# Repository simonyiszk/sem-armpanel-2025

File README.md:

# STM32F070 mikrokontrolleres ARM fejlesztőpanel a<br/> Schönherz Elektronikai Műhely 2025-ös<br/> alapozó tanfolyamához

Fícsörök:
- Kenyérvágódeszkával kompatibilis kialakítás
- Feliratozott lábak
- USB-C csatlakozó
- Integrált CMSIS-DAP programozó áramkör
- Visszajelző LED-ek: tápfeszültség, programozó/debugger üzemmód, valamint USER LED a PA6-os lábon
- RESET gomb

A mikrovezérlőhöz tartozó dokumentáció itt érhető el:<br/> [https://www.st.com/en/microcontrollers-microprocessors/stm32f070f6.html#documentation](https://www.st.com/en/microcontrollers-microprocessors/stm32f070f6.html#documentation)

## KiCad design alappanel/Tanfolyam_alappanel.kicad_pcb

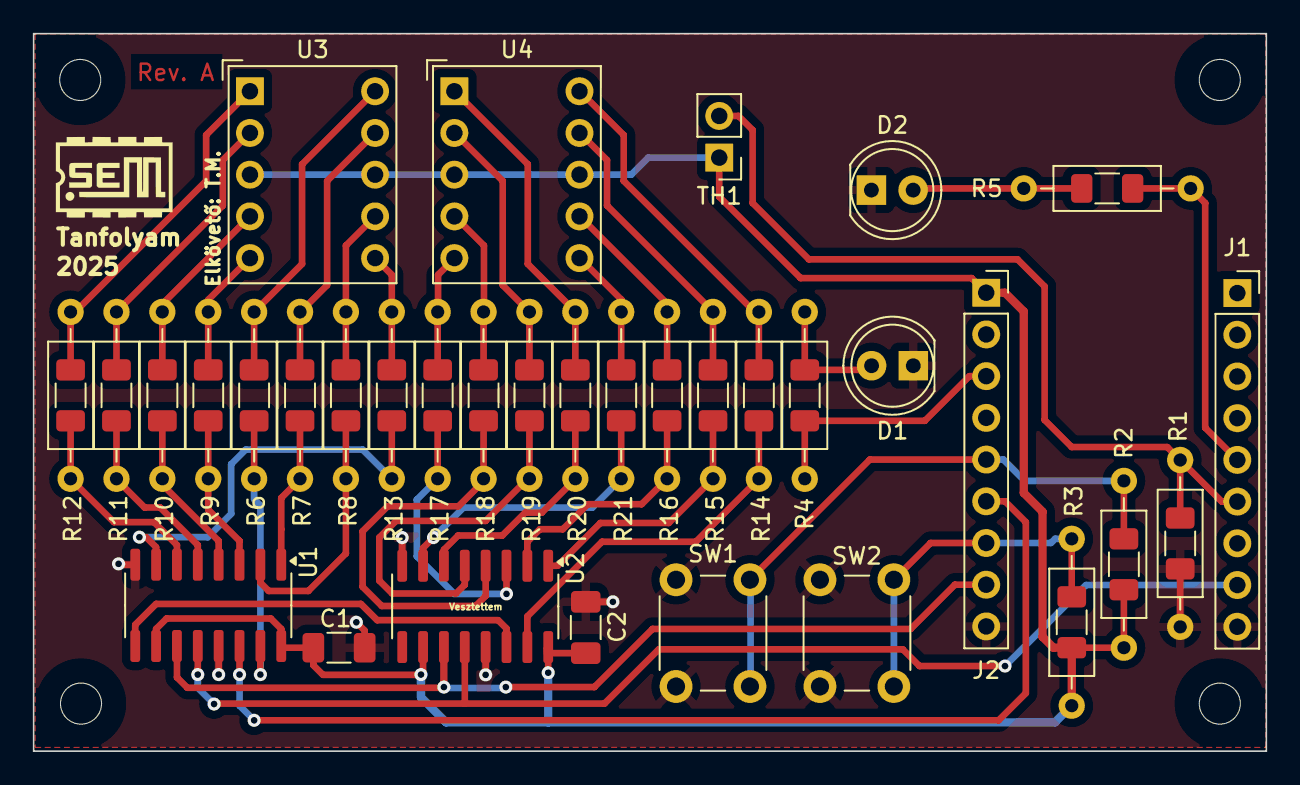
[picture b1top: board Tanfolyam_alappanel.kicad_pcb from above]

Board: 2 copper layers, 75.1 x 43.7 mm, 34 parts (0 on the bottom side), 45 nets.

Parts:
C1, C2: 100n; C_1206_3216Metric_Pad1.33x1.80mm_HandSolder
D1, D2: LED; LED_D5.0mm
J1, J2: Connector; PinSocket_1x09_P2.54mm_Vertical
R1, R2, R3: 10k; R_1206_THT
R4, R5, R6, R7, R8, R9, R10, R11, R12, R13, R14, R15, R16, R17, R18, R19, R20, R21: 220; R_1206_THT
SW1, SW2: SW_Push; SW_PUSH_6mm
TH1: NTC; PinHeader_1x02_P2.54mm_Vertical
U1, U2: 74HC595; SOIC-16_3.9x9.9mm_P1.27mm
U3, U4: SA39-11SRWA; Sx39-1xxxxx

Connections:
+3.3V: C1.1, C2.1, J2.1, R2.1, R3.1, TH1.1, U1.10 (~SRCLR), U1.16 (VCC), U2.10 (~SRCLR), U2.16 (VCC), U3.3 (CA), U3.8 (CA), U4.3 (CA), U4.8 (CA)
/PA0: J1.5, R5.1
/PA1: J1.6, R1.1, TH1.2
/PA4: J1.8, U1.12 (RCLK), U2.12 (RCLK)
/PA5: J2.8, U1.11 (SRCLK), U2.11 (SRCLK)
/PA6: J2.7, R3.2, SW2.1
/PA7: J2.6, U1.14 (SER)
/PA10: J2.3, R4.1
/PB1: J2.5, R2.2, SW1.1
GND: C1.2, C2.2, D1.1 (K), D2.1 (K), J1.9, J2.9, R1.2, SW1.2, SW2.2, U1.8 (GND), U1.13 (~OE), U2.8 (GND), U2.13 (~OE)
unnamed: D1.2 (A), R4.2
unnamed: D2.2 (A), R5.2
unnamed: R6.1, U1.15 (QA)
unnamed: R7.1, U1.1 (QB)
unnamed: R8.1, U1.2 (QC)
unnamed: R9.1, U1.3 (QD)
unnamed: R10.1, U1.4 (QE)
unnamed: R11.1, U1.5 (QF)
unnamed: R12.1, U1.6 (QG)
unnamed: U1.9 (QH'), U2.14 (SER)
unnamed: R13.1, U1.7 (QH)
unnamed: R14.1, U2.15 (QA)
unnamed: R15.1, U2.1 (QB)
unnamed: R16.1, U2.2 (QC)
unnamed: R17.1, U2.3 (QD)
unnamed: R18.1, U2.4 (QE)
unnamed: R19.1, U2.5 (QF)
unnamed: R20.1, U2.6 (QG)
unnamed: R21.1, U2.7 (QH)
unnamed: R6.2, U3.10 (A)
unnamed: R7.2, U3.9 (B)
unnamed: R8.2, U3.7 (C)
unnamed: R9.2, U3.5 (D)
unnamed: R13.2, U3.6 (DP)
unnamed: R10.2, U3.4 (E)
unnamed: R11.2, U3.2 (F)
unnamed: R12.2, U3.1 (G)
unnamed: R14.2, U4.10 (A)
unnamed: R15.2, U4.9 (B)
unnamed: R16.2, U4.7 (C)
unnamed: R17.2, U4.5 (D)
unnamed: R21.2, U4.6 (DP)
unnamed: R18.2, U4.4 (E)
unnamed: R19.2, U4.2 (F)
unnamed: R20.2, U4.1 (G)

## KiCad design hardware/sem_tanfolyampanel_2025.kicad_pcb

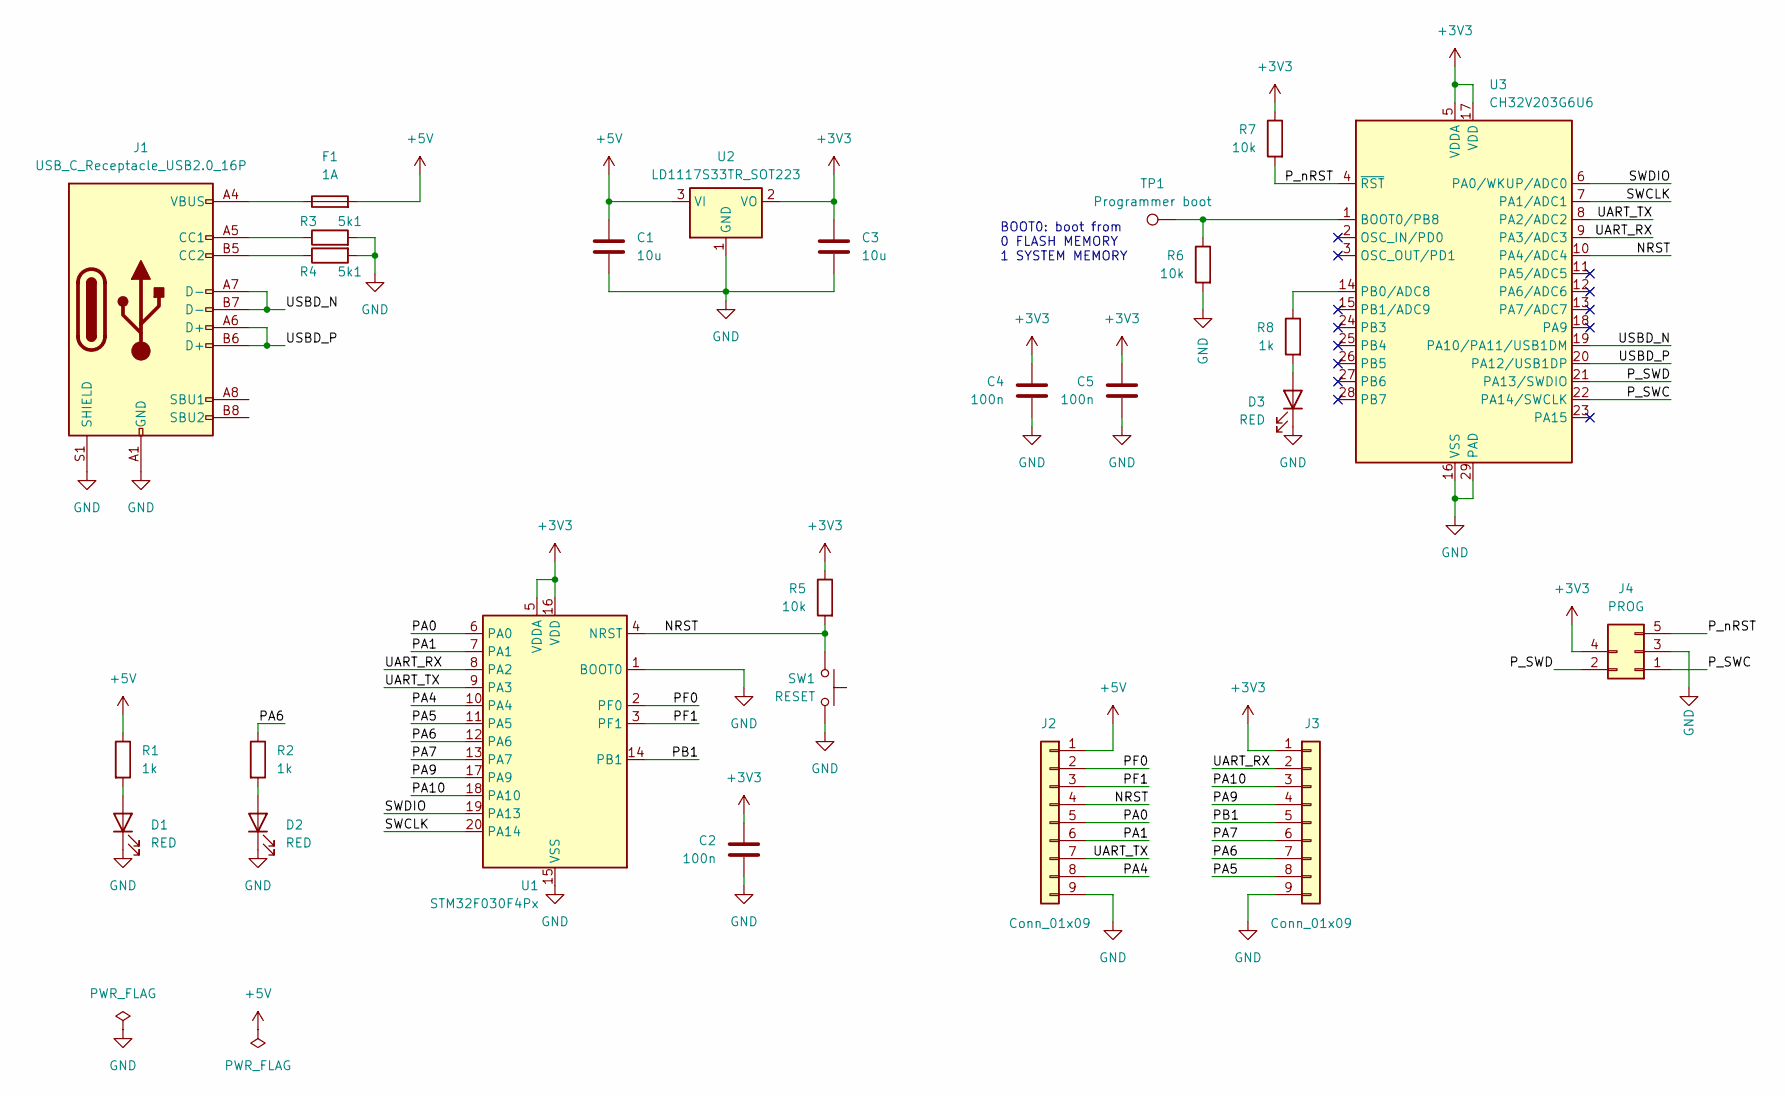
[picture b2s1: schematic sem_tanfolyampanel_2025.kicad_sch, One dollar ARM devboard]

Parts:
C1, C3: 10u; C_0805_2012Metric
C2, C4, C5: 100n; C_0603_1608Metric
D1, D2, D3: RED; LED_0603_1608Metric
F1: 1A; Fuse_1206_3216Metric
J1: USB_C_Receptacle_USB2.0_16P; USB_C_Receptacle_G-Switch_GT-USB-7010ASV
J2, J3: Conn_01x09; PinHeader_1x09_P2.54mm_Vertical
J4: PROG; ProgConnector_5pin
R1, R2, R8: 1k; R_0603_1608Metric
R3, R4: 5k1; R_0603_1608Metric
R5, R6, R7: 10k; R_0603_1608Metric
SW1: RESET; SW_SPST_TL3342
TP1: Programmer boot; TestPoint_THTPad_D1.5mm_Drill0.7mm
U1: STM32F030F4Px; TSSOP-20_4.4x6.5mm_P0.65mm
U2: LD1117S33TR_SOT223; SOT-223-3_TabPin2
U3: CH32V203G6U6; QFN-28-1EP_4x4mm_P0.4mm_EP2.8x2.8mm

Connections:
+3V3: C2.1, C3.1, C4.1, C5.1, J3.1, J4.4, R5.1, R7.1, U1.5 (VDDA), U1.16 (VDD), U2.2 (VO), U3.5 (VDDA), U3.17 (VDD)
+5V: C1.1, F1.2, J2.1, R1.1, U2.3 (VI)
/NRST: J2.4, R5.2, SW1.2, U1.4 (NRST), U3.10 (PA4/ADC4)
/PA0: J2.5, U1.6 (PA0)
/PA1: J2.6, U1.7 (PA1)
/PA4: J2.8, U1.10 (PA4)
/PA5: J3.8, U1.11 (PA5)
/PA6: J3.7, R2.1, U1.12 (PA6)
/PA7: J3.6, U1.13 (PA7)
/PA9: J3.4, U1.17 (PA9)
/PA10: J3.3, U1.18 (PA10)
/PB1: J3.5, U1.14 (PB1)
/PF0: J2.2, U1.2 (PF0)
/PF1: J2.3, U1.3 (PF1)
/P_SWC: J4.1, U3.22 (PA14/SWCLK)
/P_SWD: J4.2, U3.21 (PA13/SWDIO)
/P_nRST: J4.5, R7.2, U3.4 (~RST)
/SWCLK: U1.20 (PA14), U3.7 (PA1/ADC1)
/SWDIO: U1.19 (PA13), U3.6 (PA0/WKUP/ADC0)
/UART_RX: J3.2, U1.8 (PA2), U3.9 (PA3/ADC3)
/UART_TX: J2.7, U1.9 (PA3), U3.8 (PA2/ADC2)
/USBD_N: J1.A7 (D-), J1.B7 (D-), U3.19 (PA10/PA11/USB1DM)
/USBD_P: J1.A6 (D+), J1.B6 (D+), U3.20 (PA12/USB1DP)
GND: C1.2, C2.2, C3.2, C4.2, C5.2, D1.1 (K), D2.1 (K), D3.1 (K), J1.A1 (GND), J1.A12 (GND), J1.B1 (GND), J1.B12 (GND), J1.S1 (SHIELD), J2.9, J3.9, J4.3, R3.2, R4.2, R6.2, SW1.1, U1.1 (BOOT0), U1.15 (VSS), U2.1 (GND), U3.16 (VSS), U3.29 (PAD)
unnamed: D1.2 (A), R1.2
unnamed: D2.2 (A), R2.2
unnamed: D3.2 (A), R8.2
unnamed: F1.1, J1.A4 (VBUS), J1.A9 (VBUS), J1.B4 (VBUS), J1.B9 (VBUS)
unnamed: J1.A5 (CC1), R3.1
unnamed: J1.B5 (CC2), R4.1
unnamed: R6.1, TP1.1, U3.1 (BOOT0/PB8)
unnamed: R8.1, U3.14 (PB0/ADC8)

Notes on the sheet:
BOOT0: boot from 0 FLASH MEMORY 1 SYSTEM MEMORY

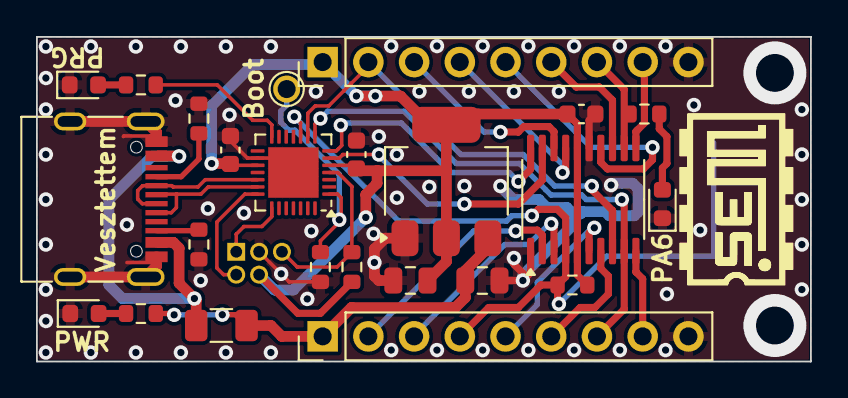
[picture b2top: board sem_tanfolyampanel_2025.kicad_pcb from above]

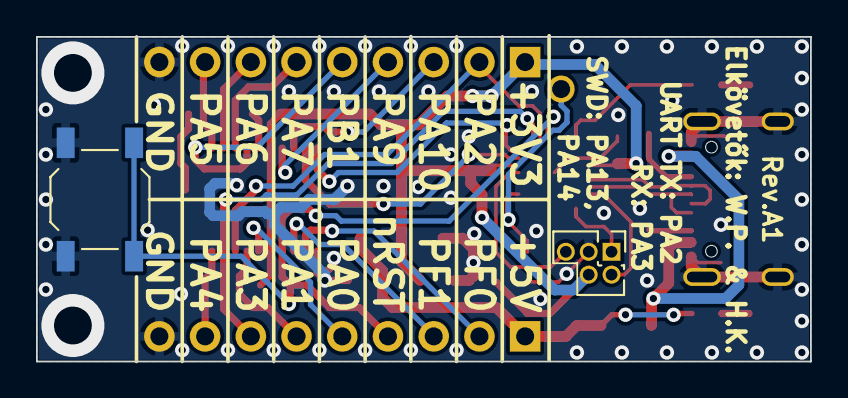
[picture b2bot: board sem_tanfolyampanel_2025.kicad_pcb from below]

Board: 2 copper layers, 43.0 x 18.0 mm, 26 parts (2 on the bottom side), 32 nets.

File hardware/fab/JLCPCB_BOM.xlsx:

Comment | Designator | Footprint | JLCPCB Part #（optional）
100n | C5,C2,C4 | C_0603_1608Metric | C14663
RED | D2,D3,D1 | LED_0603_1608Metric | C2286
LD1117S33TR_SOT223 | U2 | SOT-223-3_TabPin2 | C6186
10u | C3,C1 | C_0805_2012Metric | C15850
10k | R6,R7,R5 | R_0603_1608Metric | C25804
STM32F030F4Px | U1 | TSSOP-20_4.4x6.5mm_P0.65mm | C86951
1A | F1 | Fuse_1206_3216Metric | C883131
1k | R1,R2,R8 | R_0603_1608Metric | C21190
5k1 | R4,R3 | R_0603_1608Metric | C23186
CH32V203G6U6 | U3 | QFN-28-1EP_4x4mm_P0.4mm_EP2.8x2.8mm | C5142280
USB_C_Receptacle_USB2.0_16P | J1 | USB_C_Receptacle_G-Switch_GT-USB-7010ASV | C2927038

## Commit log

2024-12-07 Initial commit with schematic and unrouted PCB
2024-12-08 First iteration of PCB routing
2024-12-17 Rerouting and finalizing.
2024-12-26 Prototype sent to fab.
2025-01-09 Add interactive BoM for Rev.A
2025-01-11 Add config files for platformio project template
2025-01-13 Added BOM and panelization script.
2025-01-16 Rev.A1
2025-01-16 Sent to fab.
2025-02-05 Added base board. Sent to fab.
